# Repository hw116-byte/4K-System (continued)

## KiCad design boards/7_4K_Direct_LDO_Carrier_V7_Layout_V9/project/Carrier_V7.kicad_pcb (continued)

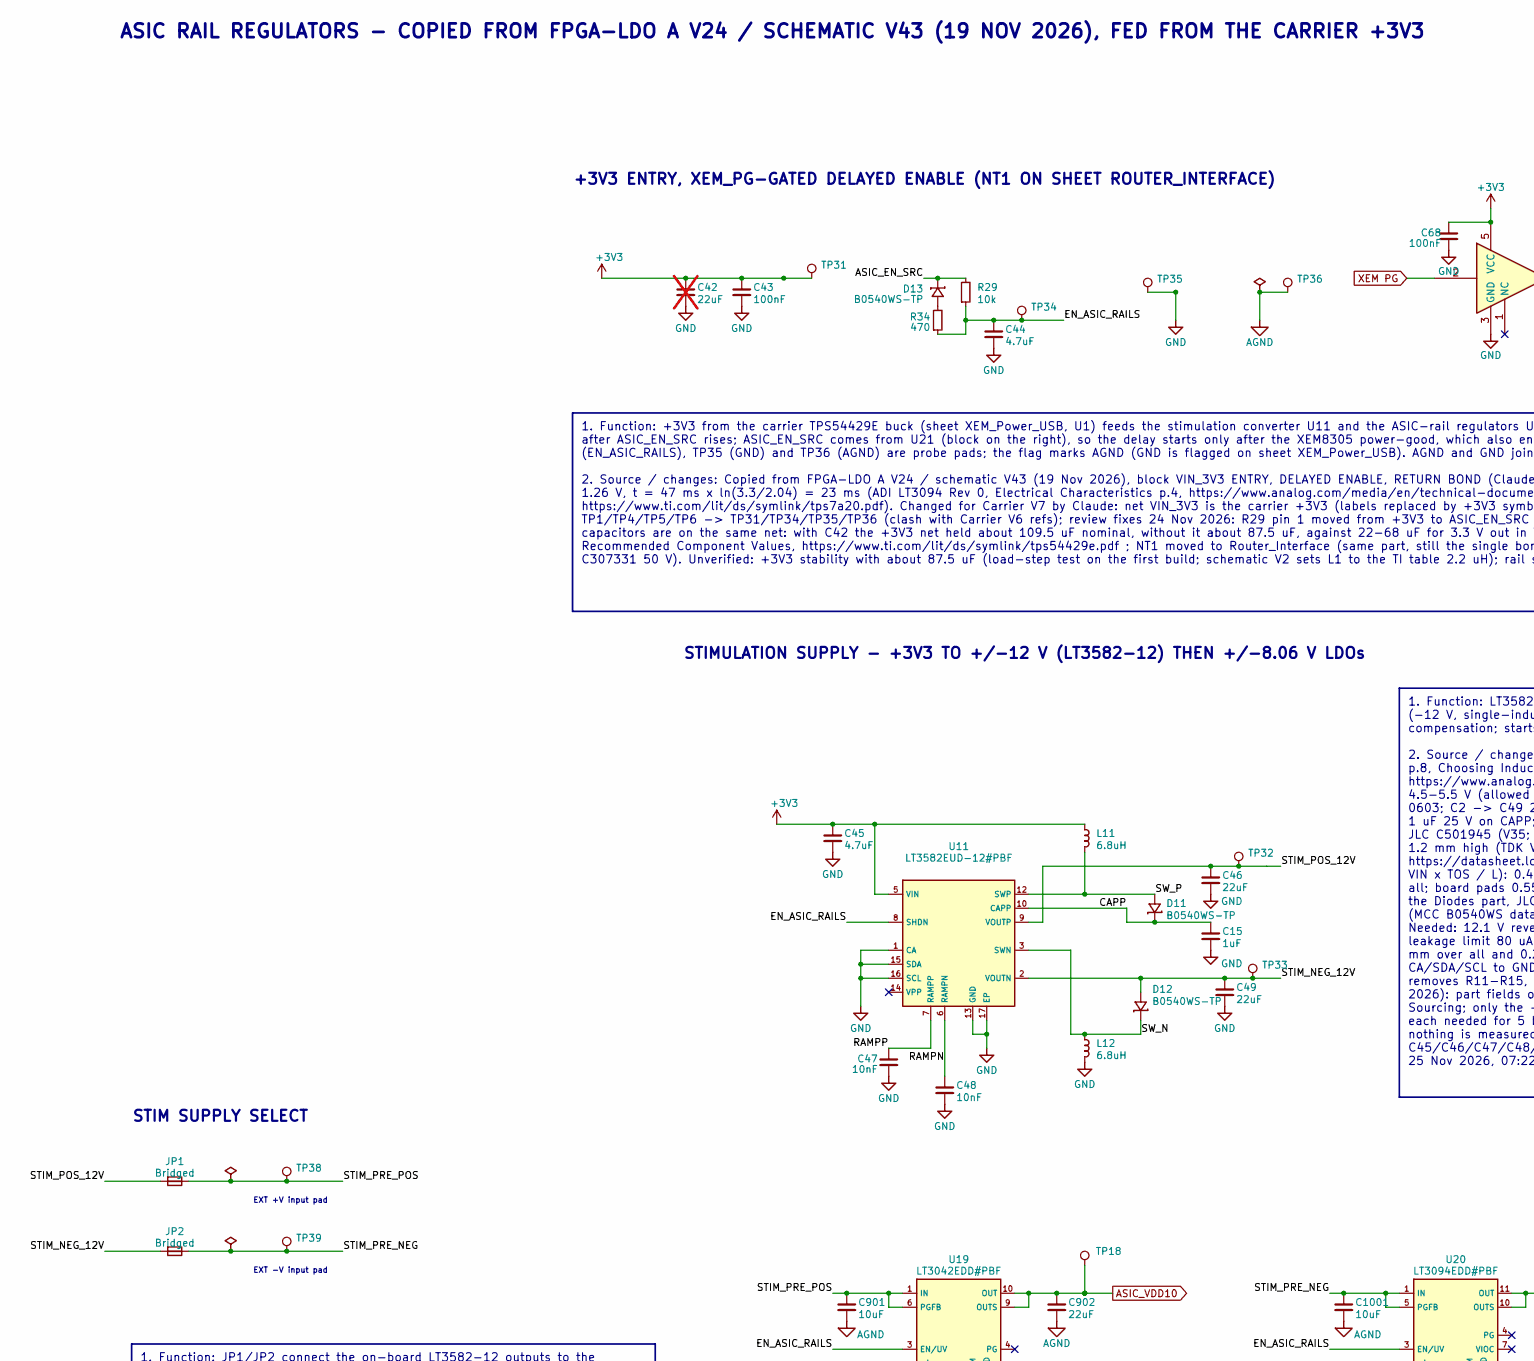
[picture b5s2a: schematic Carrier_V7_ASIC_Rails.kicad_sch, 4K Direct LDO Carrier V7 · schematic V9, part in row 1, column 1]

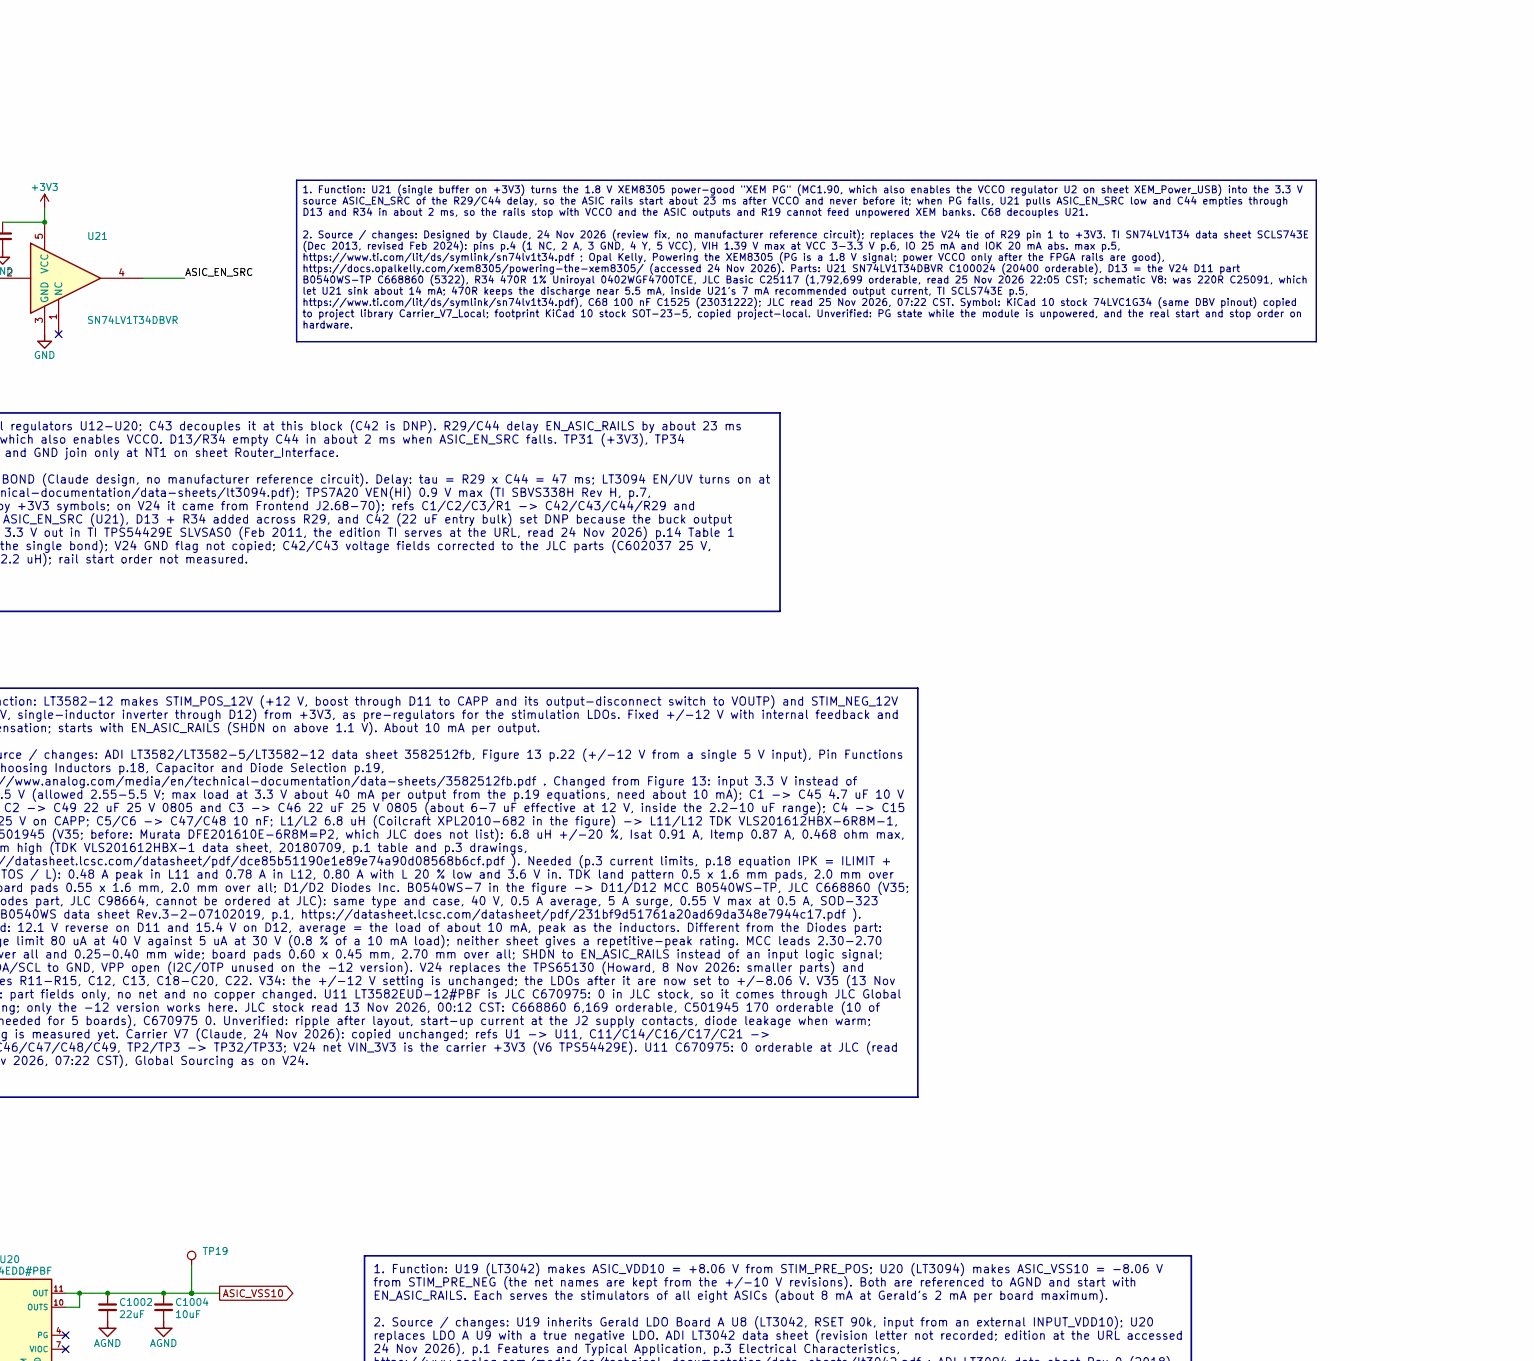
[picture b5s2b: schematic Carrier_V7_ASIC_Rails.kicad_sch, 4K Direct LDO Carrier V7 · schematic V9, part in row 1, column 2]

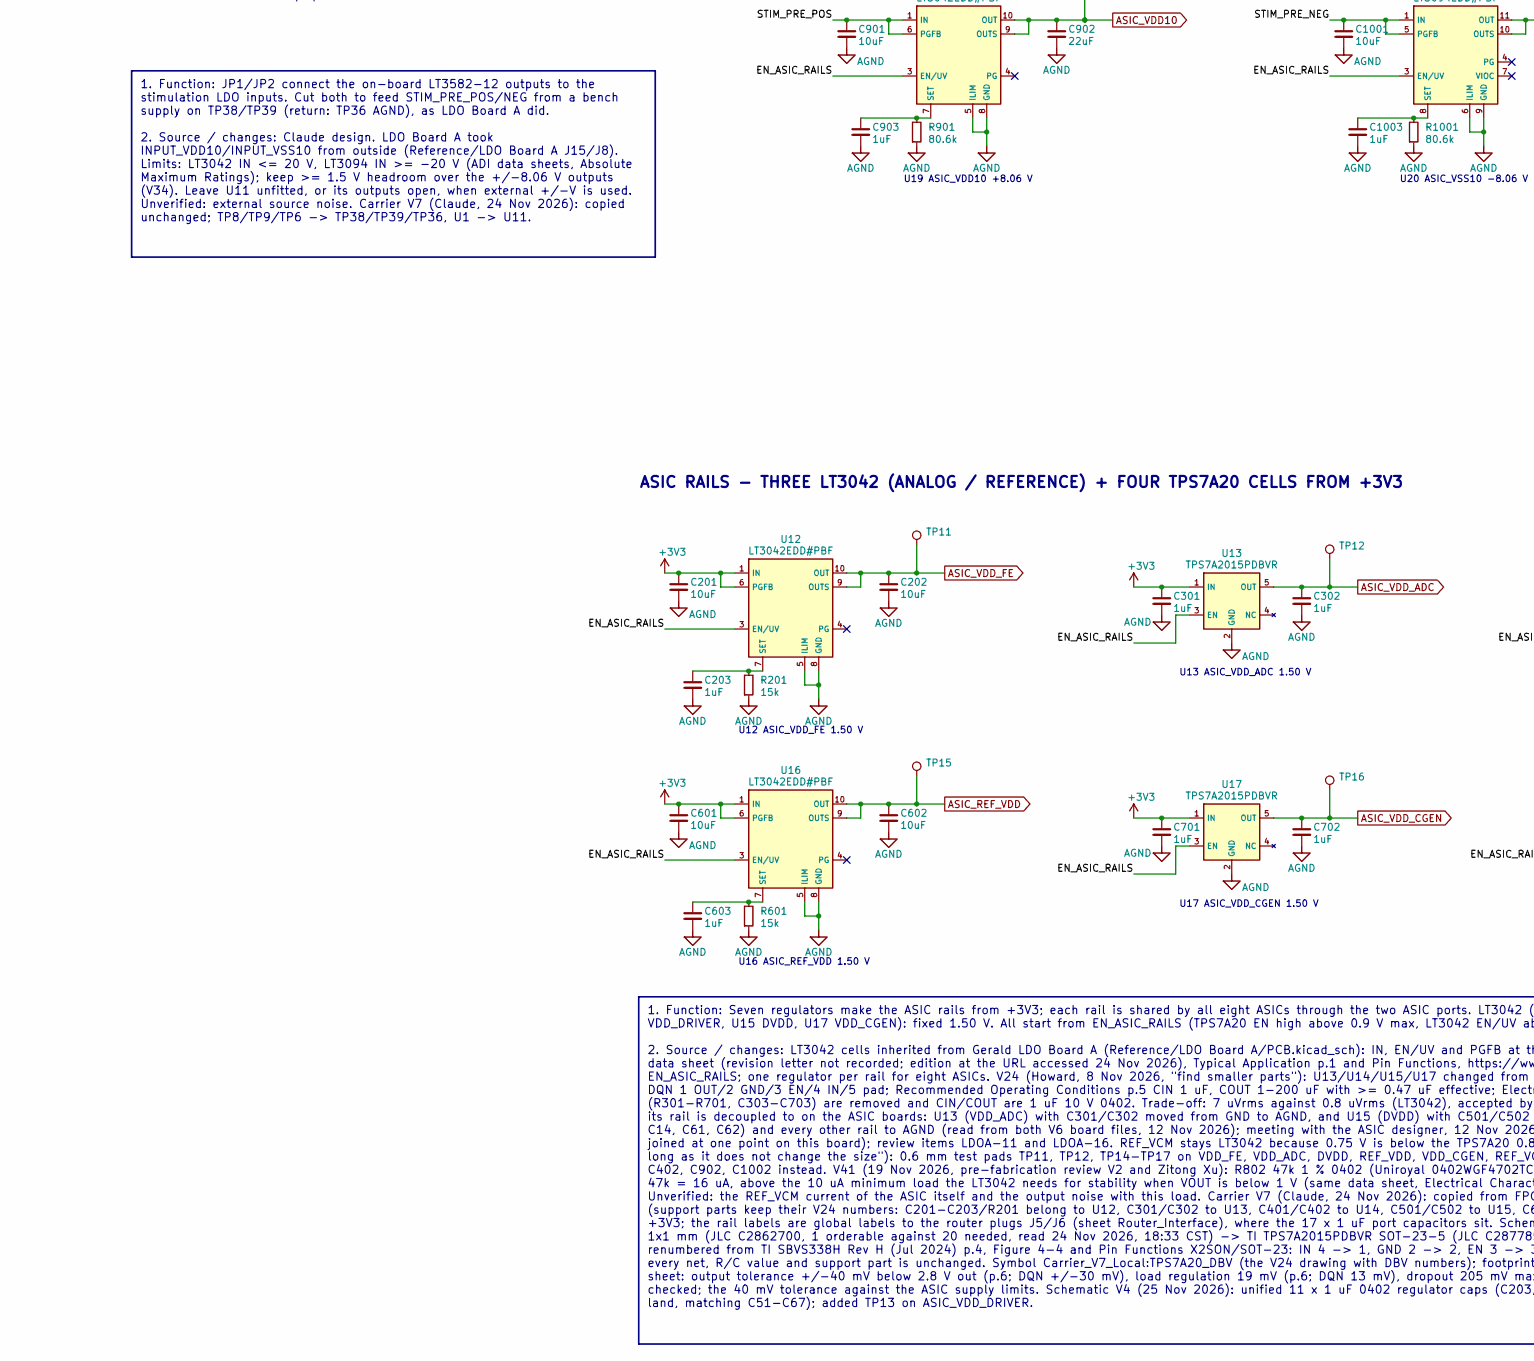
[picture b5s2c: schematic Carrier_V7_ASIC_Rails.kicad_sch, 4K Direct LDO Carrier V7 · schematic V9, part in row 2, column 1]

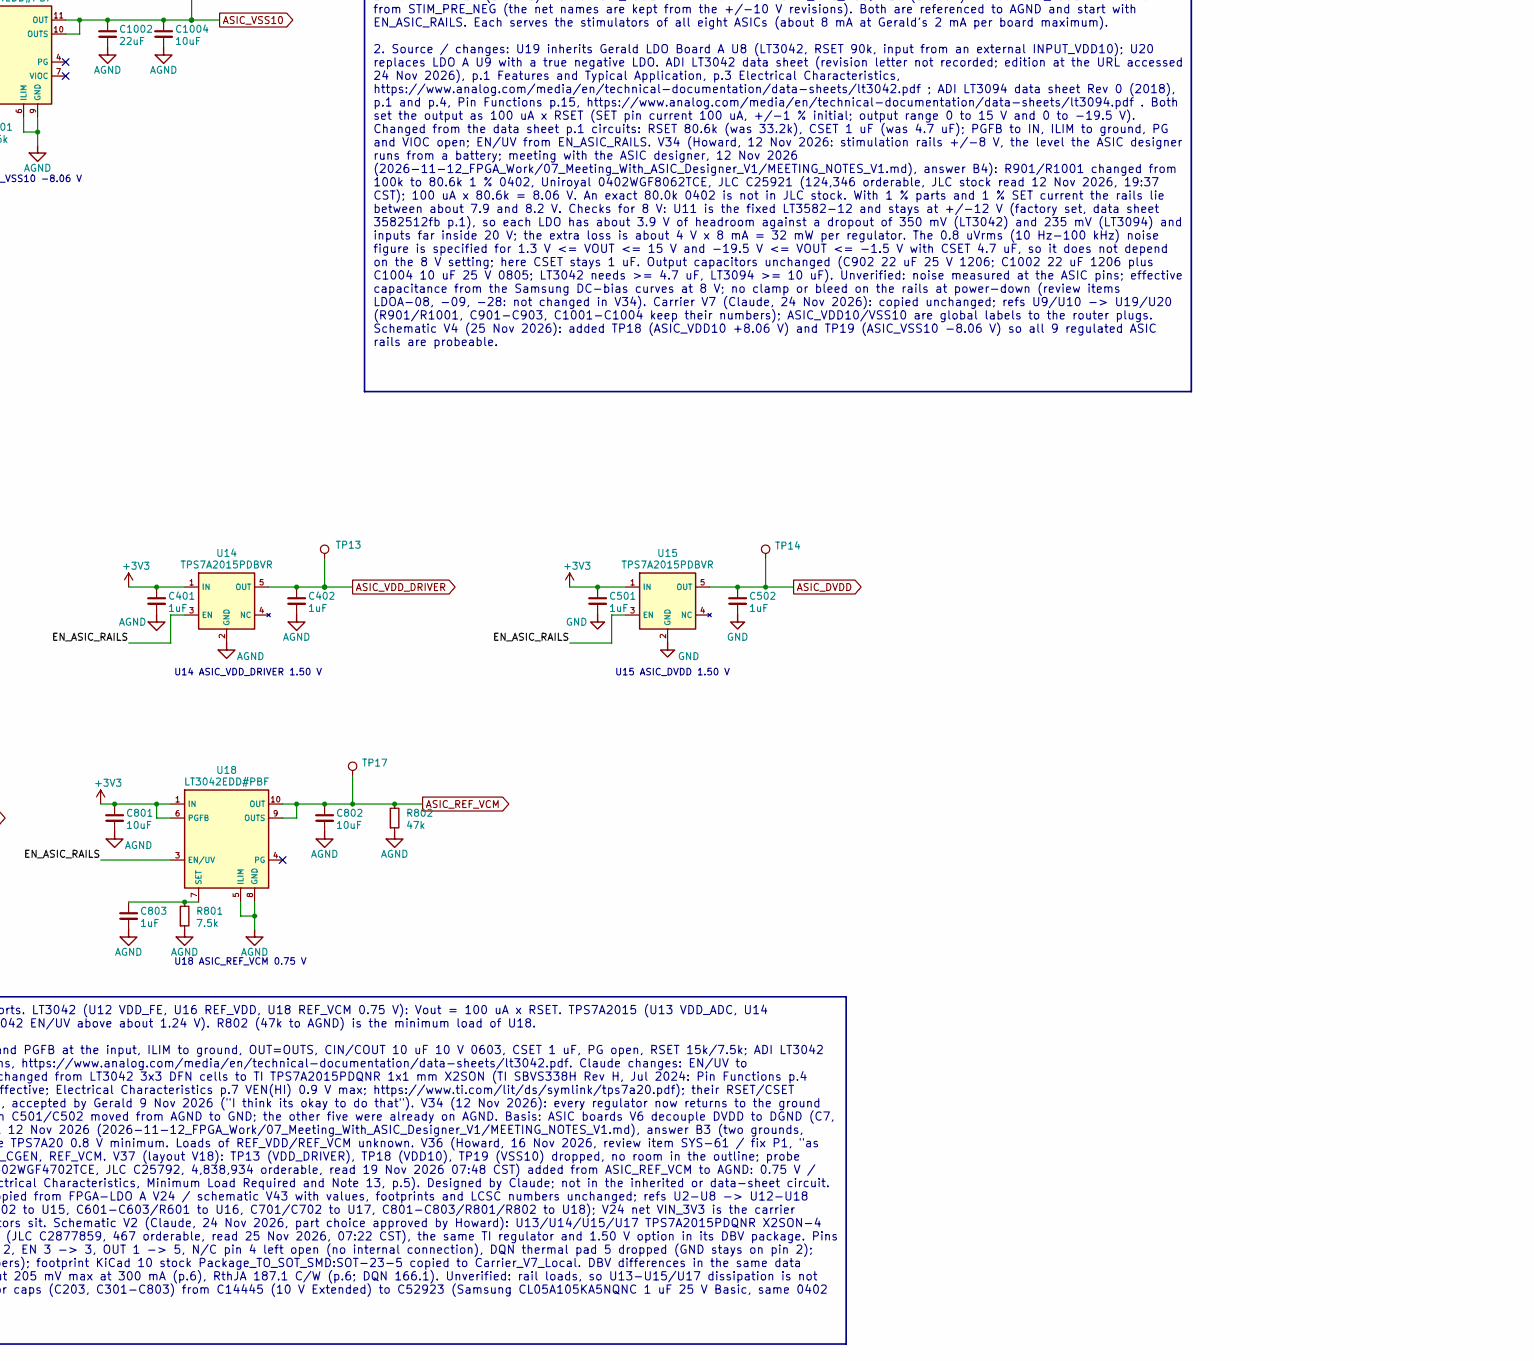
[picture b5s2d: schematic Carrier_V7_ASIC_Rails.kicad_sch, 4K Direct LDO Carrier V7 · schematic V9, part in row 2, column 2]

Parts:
C15, C903, C1003: 1uF; C_0603_1608Metric; Voltage 25V; MPN Samsung CL10A105KA8NNNC (1uF 25V X5R 06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; LCSC C5673
C42: 22uF; C_0805_2012Metric; Voltage 25V; LCSC C602037; not fitted
C43: 100nF; C_0402_1005Metric; Voltage 50V; MPN Samsung CL05B104KB54PNC (100nF 50V X7R 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; LCSC C307331
C44: 4.7uF; C_0603_1608Metric; Voltage 10V; MPN Samsung CL10A475KP8NNNC (4.7uF 10V X5R 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; LCSC C1705
C45: 4.7uF; C_0603_1608Metric; Voltage 10V; LCSC C1705
C46, C49: 22uF; C_0805_2012Metric; Voltage 25V; MPN Samsung CL21A226MAYNNNE (22uF 25V X5R 0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; LCSC C602037
C47, C48: 10nF; C_0402_1005Metric; Voltage 50V; MPN Samsung CL05B103KB5NNNC (10nF 50V X7R 0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; LCSC C15195
C68: 100nF; C_0402_1005Metric; Voltage 16V; MPN Samsung CL05B104KO5NNNC (100nF 16V X7R 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; LCSC C1525
C201, C202, C601, C602, C801, C802: 10uF; C_0603_1608Metric; Voltage 10V; MPN Samsung CL10A106KP8NNNC (10uF 10V X5R 0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; LCSC C19702
C203, C301, C302, C401, C402, C501, C502, C603, C701, C702, C803: 1uF; C_0402_1005Metric; Voltage 25V; MPN Samsung CL05A105KA5NQNC (1 uF 25 V X5R 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; LCSC C52923
C901, C1001, C1004: 10uF; C_0805_2012Metric; Voltage 25V; MPN Samsung CL21A106KAYNNNE (10uF 25V X5R 0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; LCSC C15850
C902, C1002: 22uF; C_1206_3216Metric; Voltage 25V; MPN Samsung CL31A226KAHNNNE (22uF 25V X5R 1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; LCSC C12891
D11, D12, D13: B0540WS-TP; D_SOD-323; MPN MCC B0540WS-TP (40 V 0.5 A SOD-323); LCSC C668860
JP1, JP2: Bridged; SolderJumper-2_P1.3mm_Bridged_RoundedPad1.0x1.5mm
L11, L12: 6.8uH; L_Murata_DFE201610P; MPN TDK VLS201612HBX-6R8M-1 (6.8 uH 20 %, 2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; LCSC C501945
R29: 10k; R_0402_1005Metric; Tolerance 1%; LCSC C25744
R34: 470; R_0402_1005Metric; Tolerance 1%; MPN UNI-ROYAL 0402WGF4700TCE (470R 1% 0402); LCSC C25117
R201, R601: 15k; R_0402_1005Metric; Tolerance 1%; MPN UNI-ROYAL 0402WGF1502TCE (15k 1% 0402); LCSC C25756
R801: 7.5k; R_0402_1005Metric; Tolerance 1%; MPN UNI-ROYAL 0402WGF7501TCE (7.5k 1% 0402); LCSC C25918
R802: 47k; R_0402_1005Metric; Tolerance 1%; MPN Uniroyal 0402WGF4702TCE (47k 1% 0402); LCSC C25792
R901, R1001: 80.6k; R_0402_1005Metric; Tolerance 1%; MPN Uniroyal 0402WGF8062TCE (80.6k 1% 0402); LCSC C25921
TP11: ASIC_VDD_FE; TestPoint_Pad_D0.6mm_Compact
TP12: ASIC_VDD_ADC; TestPoint_Pad_D0.6mm_Compact
TP13: ASIC_VDD_DRIVER; TestPoint_Pad_D0.6mm_Compact
TP14: ASIC_DVDD; TestPoint_Pad_D0.6mm_Compact
TP15: ASIC_REF_VDD; TestPoint_Pad_D0.6mm_Compact
TP16: ASIC_VDD_CGEN; TestPoint_Pad_D0.6mm_Compact
TP17: ASIC_REF_VCM; TestPoint_Pad_D0.6mm_Compact
TP18: ASIC_VDD10; TestPoint_Pad_D0.6mm_Compact
TP19: ASIC_VSS10; TestPoint_Pad_D0.6mm_Compact
TP31: +3V3; TestPoint_Pad_D1.0mm_Compact
TP32: STIM_POS_12V; TestPoint_Pad_D1.0mm_Compact
TP33: STIM_NEG_12V; TestPoint_Pad_D1.0mm_Compact
TP34: EN_ASIC_RAILS; TestPoint_Pad_D1.0mm_Compact
TP35: GND; TestPoint_Pad_D1.0mm_Compact
TP36: AGND; TestPoint_Pad_D1.0mm_Compact
TP38: STIM_PRE_POS; TestPoint_Pad_D1.0mm_Compact
TP39: STIM_PRE_NEG; TestPoint_Pad_D1.0mm_Compact
U11: LT3582EUD-12#PBF; QFN-16-1EP_3x3mm_P0.5mm_EP1.45x1.45mm; MPN LT3582EUD-12#PBF; LCSC C670975
U12, U16, U18, U19: LT3042EDD#PBF; DFN-10-1EP_3x3mm_P0.5mm_EP1.65x2.38mm; MPN LT3042EDD#TRPBF; LCSC C580010
U13, U14, U15, U17: TPS7A2015PDBVR; SOT-23-5; MPN TPS7A2015PDBVR; LCSC C2877859
U20: LT3094EDD#PBF; DFN-12-1EP_3x3mm_P0.45mm_EP1.65x2.38mm; MPN LT3094EDD#PBF; LCSC C670492
U21: SN74LV1T34DBVR; SOT-23-5; MPN TI SN74LV1T34DBVR; LCSC C100024

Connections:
+3V3: C42.1, C43.1, C45.1, C68.1, C201.1, C301.1, C401.1, C501.1, C601.1, C701.1, C801.1, L11.1, TP31.1, U11.5 (VIN), U12.1 (IN), U12.2 (IN), U12.6 (PGFB), U13.1 (IN), U14.1 (IN), U15.1 (IN), U16.1 (IN), U16.2 (IN), U16.6 (PGFB), U17.1 (IN), U18.1 (IN), U18.2 (IN), U18.6 (PGFB), U21.5 (VCC); also elsewhere on the board
/ASIC_Rails/ASIC_EN_SRC: D13.1 (K), R29.1, U21.4
/ASIC_Rails/CAPP: C15.1, D11.1 (K), U11.10 (CAPP), U11.11 (CAPP)
/ASIC_Rails/EN_ASIC_RAILS: C44.1, R29.2, R34.2, TP34.1, U11.8 (SHDN), U12.3 (EN/UV), U13.3 (EN), U14.3 (EN), U15.3 (EN), U16.3 (EN/UV), U17.3 (EN), U18.3 (EN/UV), U19.3 (EN/UV), U20.3 (EN/UV)
/ASIC_Rails/RAMPN: C48.1, U11.6 (RAMPN)
/ASIC_Rails/RAMPP: C47.1, U11.7 (RAMPP)
/ASIC_Rails/STIM_NEG_12V: C49.1, D12.2 (A), JP2.1, TP33.1, U11.2 (VOUTN)
/ASIC_Rails/STIM_POS_12V: C46.1, JP1.1, TP32.1, U11.9 (VOUTP)
/ASIC_Rails/STIM_PRE_NEG: C1001.1, JP2.2, TP39.1, U20.1 (IN), U20.2 (IN), U20.5 (PGFB), U20.13 (IN)
/ASIC_Rails/STIM_PRE_POS: C901.1, JP1.2, TP38.1, U19.1 (IN), U19.2 (IN), U19.6 (PGFB)
/ASIC_Rails/SW_N: D12.1 (K), L12.1, U11.3 (SWN), U11.4 (SWN)
/ASIC_Rails/SW_P: D11.2 (A), L11.2, U11.12 (SWP)
AGND: C201.2, C202.2, C203.2, C301.2, C302.2, C401.2, C402.2, C601.2, C602.2, C603.2, C701.2, C702.2, C801.2, C802.2, C803.2, C901.2, C902.2, C903.2, C1001.2, C1002.2, C1003.2, C1004.2, R201.2, R601.2, R801.2, R802.2, R901.2, R1001.2, TP36.1, U12.5 (ILIM), U12.8 (GND), U12.11 (GND), U13.2 (GND), U14.2 (GND), U16.5 (ILIM), U16.8 (GND), U16.11 (GND), U17.2 (GND), U18.5 (ILIM), U18.8 (GND), U18.11 (GND), U19.5 (ILIM), U19.8 (GND), U19.11 (GND), U20.6 (ILIM), U20.9 (GND); also elsewhere on the board
ASIC_DVDD: C502.1, TP14.1, U15.5 (OUT); also elsewhere on the board
ASIC_REF_VCM: C802.1, R802.1, TP17.1, U18.9 (OUTS), U18.10 (OUT); also elsewhere on the board
ASIC_REF_VDD: C602.1, TP15.1, U16.9 (OUTS), U16.10 (OUT); also elsewhere on the board
ASIC_VDD10: C902.1, TP18.1, U19.9 (OUTS), U19.10 (OUT); also elsewhere on the board
ASIC_VDD_ADC: C302.1, TP12.1, U13.5 (OUT); also elsewhere on the board
ASIC_VDD_CGEN: C702.1, TP16.1, U17.5 (OUT); also elsewhere on the board
ASIC_VDD_DRIVER: C402.1, TP13.1, U14.5 (OUT); also elsewhere on the board
ASIC_VDD_FE: C202.1, TP11.1, U12.9 (OUTS), U12.10 (OUT); also elsewhere on the board
ASIC_VSS10: C1002.1, C1004.1, TP19.1, U20.10 (OUTS), U20.11 (OUT), U20.12 (OUT); also elsewhere on the board
GND: C15.2, C42.2, C43.2, C44.2, C45.2, C46.2, C47.2, C48.2, C49.2, C68.2, C501.2, C502.2, L12.2, TP35.1, U11.1 (CA), U11.13 (GND), U11.15 (SDA), U11.16 (SCL), U11.17 (EP), U15.2 (GND), U21.3 (GND); also elsewhere on the board
unnamed: D13.2 (A), R34.1
unnamed: C203.1, R201.1, U12.7 (SET)
unnamed: C603.1, R601.1, U16.7 (SET)
unnamed: C803.1, R801.1, U18.7 (SET)
unnamed: C903.1, R901.1, U19.7 (SET)
unnamed: C1003.1, R1001.1, U20.8 (SET)
XEM PG: U21.2; also elsewhere on the board

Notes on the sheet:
ASIC RAILS - THREE LT3042 (ANALOG / REFERENCE) + FOUR TPS7A20 CELLS FROM +3V3
U12 ASIC_VDD_FE 1.50 V
U13 ASIC_VDD_ADC 1.50 V
U14 ASIC_VDD_DRIVER 1.50 V
U15 ASIC_DVDD 1.50 V
U16 ASIC_REF_VDD 1.50 V
U17 ASIC_VDD_CGEN 1.50 V
U18 ASIC_REF_VCM 0.75 V
1. Function: Seven regulators make the ASIC rails from +3V3; each rail is shared by all eight ASICs through the two ASIC ports. LT3042 (U12 VDD_FE, U16 REF_VDD, U18 REF_VCM 0.75 V): Vout = 100 uA x RSET. TPS7A2015 (U13 VDD_ADC, U14 VDD_DRIVER, U15 DVDD, U17 VDD_CGEN): fixed 1.50 V. All start from E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
STIMULATION SUPPLY - +3V3 TO +/-12 V (LT3582-12) THEN +/-8.06 V LDOs
1. Function: LT3582-12 makes STIM_POS_12V (+12 V, boost through D11 to CAPP and its output-disconnect switch to VOUTP) and STIM_NEG_12V (-12 V, single-inductor inverter through D12) from +3V3, as pre-regulators for the stimulation LDOs. Fixed +/-12 V with internal feedback and compensation; starts 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
U19 ASIC_VDD10 +8.06 V
U20 ASIC_VSS10 -8.06 V
1. Function: U19 (LT3042) makes ASIC_VDD10 = +8.06 V from STIM_PRE_POS; U20 (LT3094) makes ASIC_VSS10 = -8.06 V from STIM_PRE_NEG (the net names are kept from the +/-10 V revisions). Both are referenced to AGND and start with EN_ASIC_RAILS. Each serves the stimulators of all eight ASICs (about 8 mA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
STIM SUPPLY SELECT
EXT +V input pad
EXT -V input pad
1. Function: JP1/JP2 connect the on-board LT3582-12 outputs to the stimulation LDO inputs. Cut both to feed STIM_PRE_POS/NEG from a bench supply on TP38/TP39 (return: TP36 AGND), as LDO Board A did. 2. Source / changes: Claude design. LDO Board A took INPUT_VDD10/INPUT_VSS10 from outside (Reference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
+3V3 ENTRY, XEM_PG-GATED DELAYED ENABLE (NT1 ON SHEET ROUTER_INTERFACE)
1. Function: +3V3 from the carrier TPS54429E buck (sheet XEM_Power_USB, U1) feeds the stimulation converter U11 and the ASIC-rail regulators U12-U20; C43 decouples it at this block (C42 is DNP). R29/C44 delay EN_ASIC_RAILS by about 23 ms after ASIC_EN_SRC rises; ASIC_EN_SRC comes from U21 (block on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
1. Function: U21 (single buffer on +3V3) turns the 1.8 V XEM8305 power-good "XEM PG" (MC1.90, which also enables the VCCO regulator U2 on sheet XEM_Power_USB) into the 3.3 V source ASIC_EN_SRC of the R29/C44 delay, so the ASIC rails start about 23 ms after VCCO and never before it; when PG falls, U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
ASIC RAIL REGULATORS - COPIED FROM FPGA-LDO A V24 / SCHEMATIC V43 (19 NOV 2026), FED FROM THE CARRIER +3V3
